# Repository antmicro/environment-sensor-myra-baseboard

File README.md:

# Environment Sensor MYRA SiP Baseboard
Copyright (c) 2024 [Antmicro](https://www.antmicro.com/)

## Overview

This repository contains open hardware design files for Antmicro's Environment Sensor Board variant which includes the [MYRA SiP](https://github.com/antmicro/myra-sip) as well as temperature, pressure and humidity sensors.

The design files were prepared in KiCad 7.

## Key features

* Environment sensor SiP (with STM32G491REI6 MCU, 128kB FRAM, FTDI FT231XQ USB to UART converter)
* 50 mm x 26.5 mm PCB size
* USB-C Connector for data and power
* SHT45 temperature + humidity sensor:
	* typical relative humidity accuracy ±1% RH
	* operating relative humidity range 0-100% RH
	* typical temperature accuracy ±0.1°C
	* operating temperature range -40-125°C
* BME280 temperature + humidity + pressure sensor:
	* typical relative humidity accuracy ±3% RH
	* operating relative humidity range 10-100% RH
	* typical temperature accuracy ±1°C
	* operating temperature range -40-85°C
	* typical pressure accuracy ±1 hPa
	* operating pressure range 300-1100 hPa
* QWIIC Connectors
* RTC battery backup

## Repository structure

The main repository directory contains KiCad PCB project files, a LICENSE, and a README.
The remaining files are stored in the following directories:

* `doc` - contains board schematic
* `assets` - contains visual assets for showcasing this design on [Open Hardware Portal](https://openhardware.antmicro.com/boards/environment-sensor-sip-baseboard/?tab=features&view=top-ortho).

## Licensing
This project is published under the [Apache-2.0](https://github.com/antmicro/environment-sensor-sip-baseboard//blob/main/LICENSE) license.

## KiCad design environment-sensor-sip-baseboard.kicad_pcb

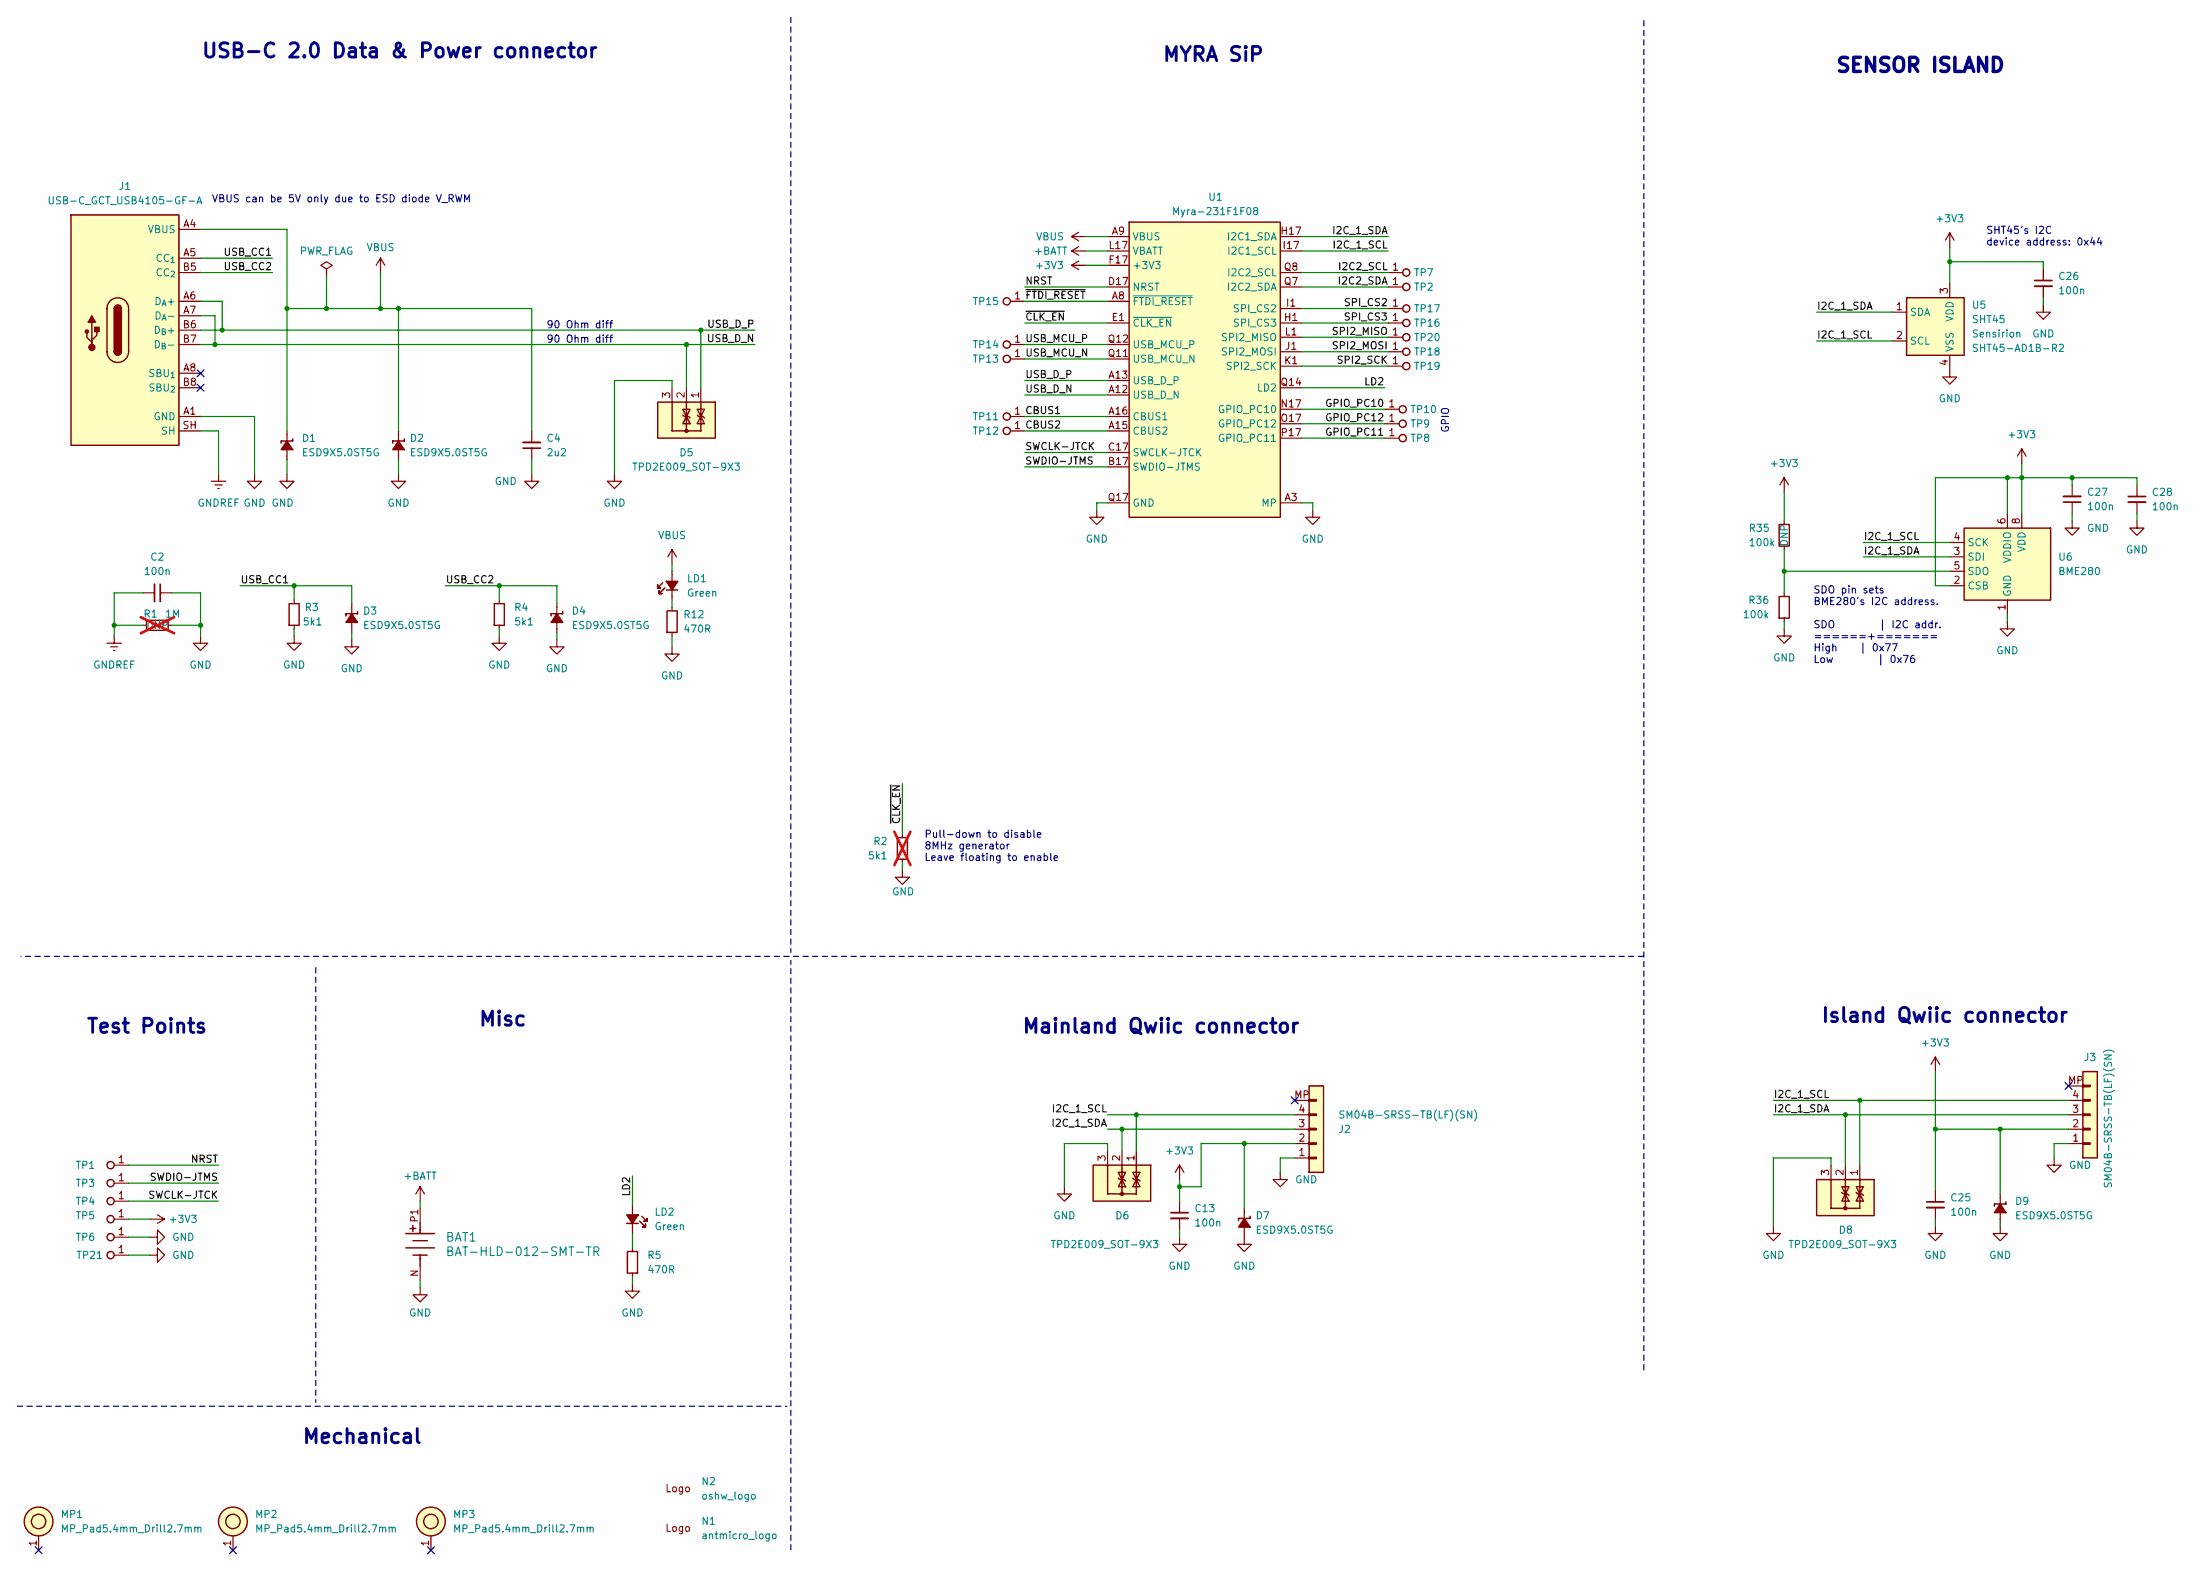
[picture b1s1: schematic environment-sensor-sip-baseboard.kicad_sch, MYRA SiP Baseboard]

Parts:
BAT1: BAT-HLD-012-SMT-TR; BAT_BAT-HLD-012-SMT-TR; MPN BAT-HLD-012-SMT-TR
C2, C13, C25, C26, C27, C28: C_100n_0402; C_0402_1005Metric; Voltage 50V; MPN GRM155R61H104KE14D
C4: C_2u2_0402; C_0402_1005Metric; MPN C1005X5R1A225K050BC
D1, D2, D3, D4, D7, D9: ESD9X5.0ST5G; SOD-923; MPN ESD9X5.0ST5G
D5, D6, D8: TPD2E009_SOT-9X3; SOT-723; MPN TPD2E009DRTR
J1: USB-C_GCT_USB4105-GF-A; USB-C_Receptacle_GCT_USB4105-GF-A; MPN USB4105-GF-A
J2, J3: JST_SH_1x4_SM04B-SRSS-TB-LF-SN; Conn_JST_SH_1x4_SM04B-SRSS-TB-LF-SN; MPN SM04B-SRSS-TB(LF)(SN)
LD1, LD2: LED_G_0603_KP-1608ZGC; LED_0603_1608Metric_G; MPN KP-1608ZGC
MP1, MP2, MP3: MP_Pad5.4mm_Drill2.7mm
N1: antmicro_logo; antmicro-logo_scaled_12mm
N2: oshw_logo; oshw-logo
R1: R_1M_0402; R_0402_1005Metric; Tolerance 1%; MPN CR0402-FX-1004GLF; not fitted
R2: R_5k1_0402; R_0402_1005Metric; Tolerance 1%; MPN CR0402-FX-5101GLF; not fitted
R3, R4: R_5k1_0402; R_0402_1005Metric; Tolerance 1%; MPN CR0402-FX-5101GLF
R5, R12: R_470R_0402; R_0402_1005Metric; Tolerance 1%; MPN CR0402-FX-4700GLF
R35, R36: R_100k_0402; R_0402_1005Metric; Tolerance 1%; MPN CR0402-FX-1003GLF
TP1, TP2, TP3, TP4, TP5, TP6, TP7, TP8, TP9, TP10, TP11, TP12, TP13, TP14, TP15, TP16, TP17, TP18, TP19, TP20, TP21: TP_1.5mm_SMD; TP_SMD_1.5mm
U1: Myra-231F1F08; LGA-64_11.4x11.4mm_Myra; MPN Myra-231F1F08
U5: SHT45; Sensirion_DFN-4-1.5x1.5x0.5mm_P0.8mm; MPN SHT45-AD1B-R2
U6: BME280; LGA-8_2.5x2.5mm_BME280; MPN BME280

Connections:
+3V3: C13.1, C25.1, C26.1, C27.2, C28.1, D7.1 (C), D9.1 (C), J2.2, J3.2, R35.1, TP5.1, U1.F17 (+3V3), U1.Q6 (+3V3), U5.3 (VDD), U6.2 (CSB), U6.6 (VDDIO), U6.8 (VDD)
+BATT: BAT1.P1, BAT1.P2, U1.L17 (VBATT)
/CBUS1: TP11.1, U1.A16 (CBUS1)
/CBUS2: TP12.1, U1.A15 (CBUS2)
/GPIO_PC10: TP10.1, U1.N17 (GPIO_PC10)
/GPIO_PC11: TP8.1, U1.P17 (GPIO_PC11)
/GPIO_PC12: TP9.1, U1.O17 (GPIO_PC12)
/I2C2_SCL: TP7.1, U1.Q8 (I2C2_SCL)
/I2C2_SDA: TP2.1, U1.Q7 (I2C2_SDA)
/I2C_1_SCL: D6.1, D8.1, J2.4, J3.4, U1.I17 (I2C1_SCL), U5.2 (SCL), U6.4 (SCK)
/I2C_1_SDA: D6.2, D8.2, J2.3, J3.3, U1.H17 (I2C1_SDA), U5.1 (SDA), U6.3 (SDI)
/LD2: LD2.2 (A), U1.Q14 (LD2)
/NRST: TP1.1, U1.D17 (NRST)
/SPI2_MISO: TP20.1, U1.L1 (SPI2_MISO)
/SPI2_MOSI: TP18.1, U1.J1 (SPI2_MOSI)
/SPI2_SCK: TP19.1, U1.K1 (SPI2_SCK)
/SPI_CS2: TP17.1, U1.I1 (SPI_CS2)
/SPI_CS3: TP16.1, U1.H1 (SPI_CS3)
/SWCLK-JTCK: TP4.1, U1.C17 (SWCLK-JTCK)
/SWDIO-JTMS: TP3.1, U1.B17 (SWDIO-JTMS)
/USB_CC1: D3.1 (C), J1.A5 (CC_{1}), R3.2
/USB_CC2: D4.1 (C), J1.B5 (CC_{2}), R4.2
/USB_D_N: D5.2, J1.A7 (D_{A}-), J1.B7 (D_{B}-), U1.A12 (USB_D_N)
/USB_D_P: D5.1, J1.A6 (D_{A}+), J1.B6 (D_{B}+), U1.A13 (USB_D_P)
/USB_MCU_N: TP13.1, U1.Q11 (USB_MCU_N)
/USB_MCU_P: TP14.1, U1.Q12 (USB_MCU_P)
/~CLK_EN: R2.2, U1.E1 (~CLK_EN)
/~FTDI_RESET: TP15.1, U1.A8 (~FTDI_RESET)
GND: BAT1.N, C2.1, C4.1, C13.2, C25.2, C26.2, C27.1, C28.2, D1.2 (A), D2.2 (A), D3.2 (A), D4.2 (A), D5.3, D6.3, D7.2 (A), D8.3, D9.2 (A), J1.A1 (GND), J1.A12 (GND), J1.B1 (GND), J1.B12 (GND), J2.1, J3.1, R1.2, R2.1, R3.1, R4.1, R5.1, R12.1, R36.1, TP6.1, TP21.1, U1.A1 (MP), U1.A2 (MP), U1.A3 (MP), U1.A4 (MP), U1.A5 (MP), U1.A6 (MP), U1.A7 (GND), U1.A11 (GND), U1.A14 (GND), U1.A17 (GND), U1.B1 (MP), U1.C1 (MP), U1.D1 (GND), U1.E17 (GND), U1.F1 (GND), U1.G1 (GND), U1.G17 (GND), U1.J17 (GND), U1.K17 (GND), U1.M1 (GND), U1.M17 (GND), U1.Q5 (GND), U1.Q9 (GND), U1.Q10 (GND), U1.Q13 (GND), U1.Q15 (GND), U1.Q16 (GND), U1.Q17 (GND), U5.4 (VSS), U6.1 (GND), U6.7 (GND)
GNDREF: C2.2, J1.SH, R1.1
unnamed: LD1.1 (C), R12.2
unnamed: LD2.1 (C), R5.2
unnamed: R35.2, R36.2, U6.5 (SDO)
VBUS: C4.2, D1.1 (C), D2.1 (C), J1.A4 (VBUS), J1.A9 (VBUS), J1.B4 (VBUS), J1.B9 (VBUS), LD1.2 (A), U1.A9 (VBUS), U1.A10 (VBUS)

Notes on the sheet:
Island Qwiic connector
MYRA SiP
90 Ohm diff
USB-C 2.0 Data & Power connector
SDO pin sets BME280's I2C address. SDO | I2C addr. ======+======= High | 0x77 Low | 0x76
VBUS can be 5V only due to ESD diode V_RWM
Pull-down to disable 8MHz generator Leave floating to enable
Misc
SENSOR ISLAND
SHT45's I2C device address: 0x44
Mainland Qwiic connector
Test Points
Mechanical
GPIO

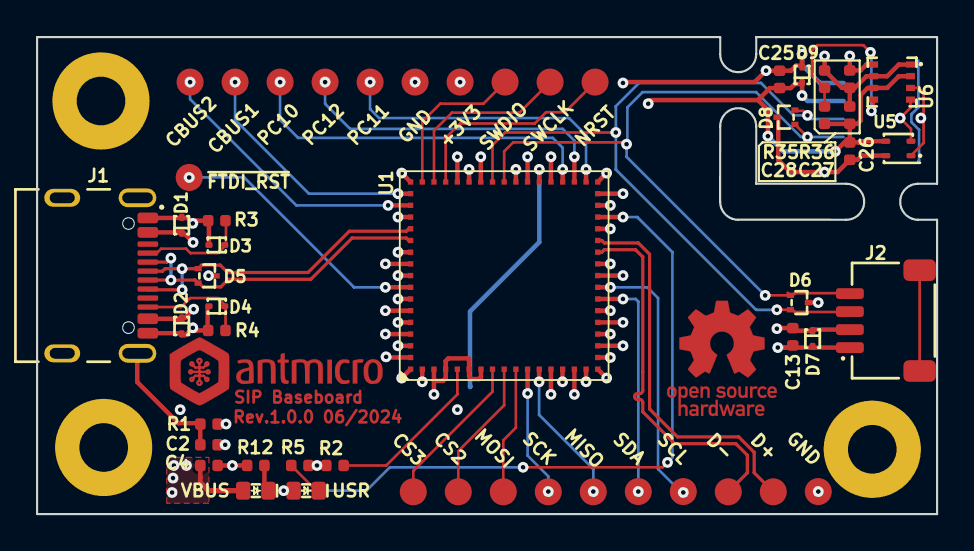
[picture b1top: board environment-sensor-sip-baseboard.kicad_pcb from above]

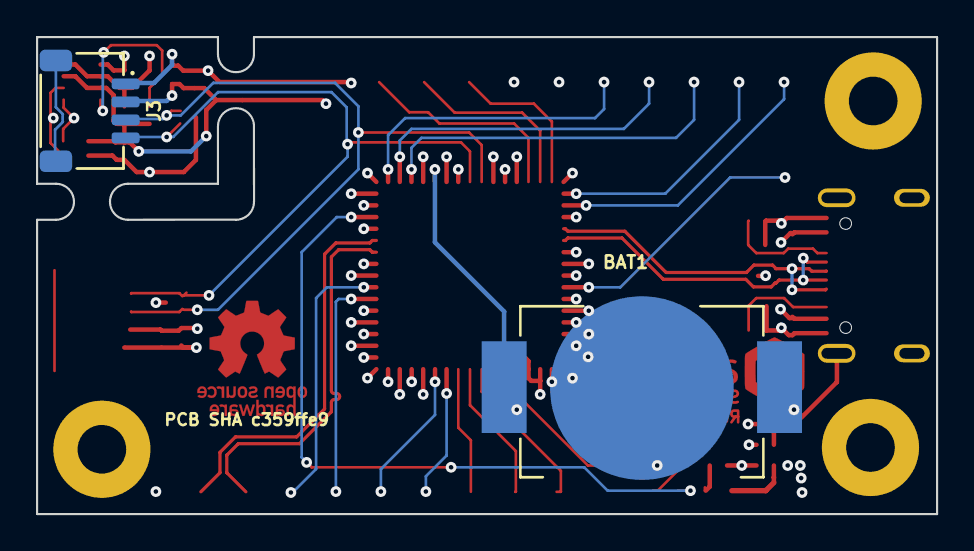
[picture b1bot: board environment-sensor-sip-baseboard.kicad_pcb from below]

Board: 4 copper layers, 50.0 x 26.5 mm, 59 parts (2 on the bottom side), 34 nets.

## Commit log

2024-06-27 [#61553] Initial commit. Create schematic
2024-06-27 [#61553] Start PCB placement
2024-06-28 [#61553] Route PCB
2024-06-28 [#61553] Improve schematic readability
2024-06-28 [#61553] Update title block
2024-06-28 [#61553] Fix ERC
2024-06-28 [#61553] Fix logo at PCB
2024-06-28 [#61553] Fill polygons
2024-07-02 [#61553] Add README.md
2024-07-02 [#61553] Fix typo in README.md
2024-07-12 [#62396] Update components
2024-07-12 [#62396] Update MYRA Description
2024-07-12 [#62396] Fix ERC and DRC
2024-07-15 [#62396] Update title block
2024-07-16 [#62396] Update SiP
2024-07-16 [#62396] Update README
2024-07-22 [#62396] Update visualization
2024-07-29 [#62840] Prepare assets
2024-07-30 Updates to README
2024-07-30 Update README image
2024-08-05 [#63457] Unify silkscreen orientation

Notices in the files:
parts and their libraries:
License: Apache-2.0
Copyright (c) 2022 Antmicro  [Apache 2.0 License](https://www.apache.org/licenses/LICENSE-2.0)
